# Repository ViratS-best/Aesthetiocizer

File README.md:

# Aesthetiocizer

Voice-controlled car firmware and hardware design for the Seeed XIAO RP2040. The firmware captures microphone audio, runs an Edge Impulse model, and uses recognized commands to control the car.

## Design

## Commands

The firmware responds to classifications with confidence of at least 0.85:
- `drive` starts the motors.
- `stop` stops the motors.
- `music` plays a melody through the speaker.
- `lights` flashes the LEDs.

## Project Contents

- `example-standalone-inferencing-pico-main/` contains the Pico application and its Edge Impulse inference sources.
- `viratsuper6-project-1-cpp-mcu-v1-impulse-#1/` contains the exported Edge Impulse model and inference SDK files.
- `design/` contains the KiCad schematic, PCB, project, BOM.csv, Gerber.zip, and 3D board export.
- `Screenshot *.png` files show project images.

## Bill of Materials (BOM)

| Part | Qty | Unit | Total | Vendor |
| :--- | :---: | :---: | :---: | :--- |
| [PCB Connection between all parts](https://www.jlcpcb.com) | 5 | $0.80 | $4.00 | [JLCPCB](https://www.jlcpcb.com) |
| [Seeed Studio XIAO RP2040 Microcontroller](https://www.amazon.com/dp/B0DRNTQ338) | 1 | $10.99 | $10.99 | [Amazon](https://www.amazon.com) |
| [Digital MEMS Microphone Module with PDM Output, MP34DT01](https://www.amazon.com/dp/B0HKML3MT8) | 1 | $9.29 | $9.29 | [Amazon](https://www.amazon.com) |
| Tax & shipping for the order | – | – | $5.00 | – |
| **Total** | | | **$29.28** | |

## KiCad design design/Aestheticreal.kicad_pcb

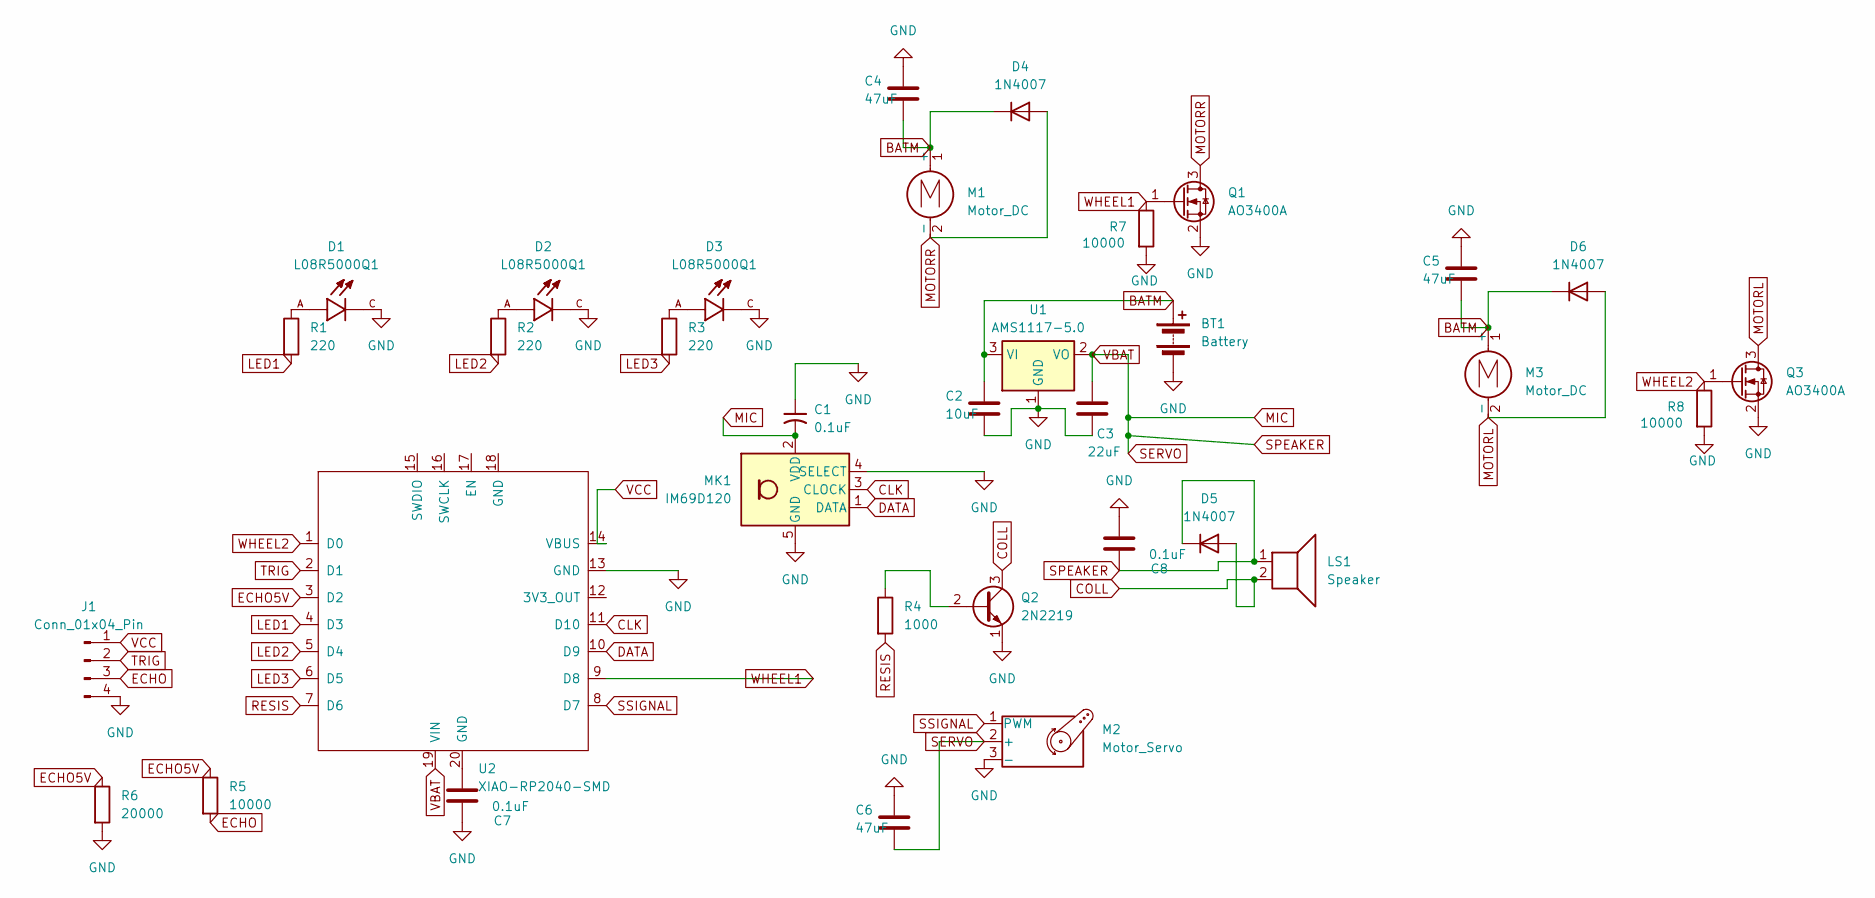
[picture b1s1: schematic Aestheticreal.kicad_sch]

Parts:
BT1: Battery; TerminalBlock_Phoenix_PT-1,5-2-3.5-H_1x02_P3.50mm_Horizontal
C1, C7, C8: 0.1uF; C_0805_2012Metric_Pad1.18x1.45mm_HandSolder
C2: 10uF; C_0805_2012Metric_Pad1.18x1.45mm_HandSolder
C3: 22uF; C_0805_2012Metric_Pad1.18x1.45mm_HandSolder
C4, C5, C6: 47uF; C_0805_2012Metric_Pad1.18x1.45mm_HandSolder
D1, D2, D3: L08R5000Q1; LEDRD254W57D500H1070; PARTREV NA
D4, D5, D6: 1N4007; D_DO-41_SOD81_P10.16mm_Horizontal
J1: Conn_01x04_Pin; PinHeader_1x04_P2.54mm_Vertical
LS1: Speaker; PinHeader_1x02_P2.54mm_Vertical
M1, M3: Motor_DC; TerminalBlock_Phoenix_PT-1,5-2-3.5-H_1x02_P3.50mm_Horizontal
M2: Motor_Servo; PinHeader_1x03_P2.54mm_Vertical
MK1: IM69D120; Infineon_PG-LLGA-5-1
Q1, Q3: AO3400A; SOT-23
Q2: 2N2219; TO-39-3
R1, R2, R3: 220; R_Axial_DIN0204_L3.6mm_D1.6mm_P5.08mm_Horizontal
R4: 1000; R_Axial_DIN0204_L3.6mm_D1.6mm_P5.08mm_Horizontal
R5, R7, R8: 10000; R_Axial_DIN0204_L3.6mm_D1.6mm_P5.08mm_Horizontal
R6: 20000; R_Axial_DIN0204_L3.6mm_D1.6mm_P5.08mm_Horizontal
U1: AMS1117-5.0; SOT-223-3_TabPin2
U2: XIAO-RP2040-SMD

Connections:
BATM: BT1.1 (+), C2.1, C4.2, C5.2, D4.1 (K), D6.1 (K), M1.1 (+), M3.1 (+), U1.3 (VI)
CLK: MK1.3 (CLOCK), U2.11 (D10)
COLL: D5.2 (A), LS1.2, Q2.3 (C)
DATA: MK1.1 (DATA), U2.10 (D9)
ECHO: J1.3, R5.2
ECHO5V: R5.1, R6.1, U2.3 (D2)
GND: BT1.2 (-), C1.1, C2.2, C3.2, C4.1, C5.1, C6.1, C7.2, C8.1, D1.C, D2.C, D3.C, J1.4, M2.3 (-), MK1.4 (SELECT), MK1.5 (GND), Q1.2 (S), Q2.1 (E), Q3.2 (S), R6.2, R7.2, R8.2, U1.1 (GND), U2.13 (GND)
LED1: R1.2, U2.4 (D3)
LED2: R2.2, U2.5 (D4)
LED3: R3.2, U2.6 (D5)
MIC: C1.2, C3.1, C6.2, C8.2, D5.1 (K), LS1.1, M2.2 (+), MK1.2 (VDD), U1.2 (VO), U2.19 (VIN)
MOTORL: D6.2 (A), M3.2 (-), Q3.3 (D)
MOTORR: D4.2 (A), M1.2 (-), Q1.3 (D)
unnamed: C7.1, U2.20 (GND)
unnamed: D1.A, R1.1
unnamed: D2.A, R2.1
unnamed: D3.A, R3.1
unnamed: Q2.2 (B), R4.1
RESIS: R4.2, U2.7 (D6)
SSIGNAL: M2.1 (PWM), U2.8 (D7)
TRIG: J1.2, U2.2 (D1)
VCC: J1.1, U2.14 (VBUS)
WHEEL1: Q1.1 (G), R7.1, U2.9 (D8)
WHEEL2: Q3.1 (G), R8.1, U2.1 (D0)

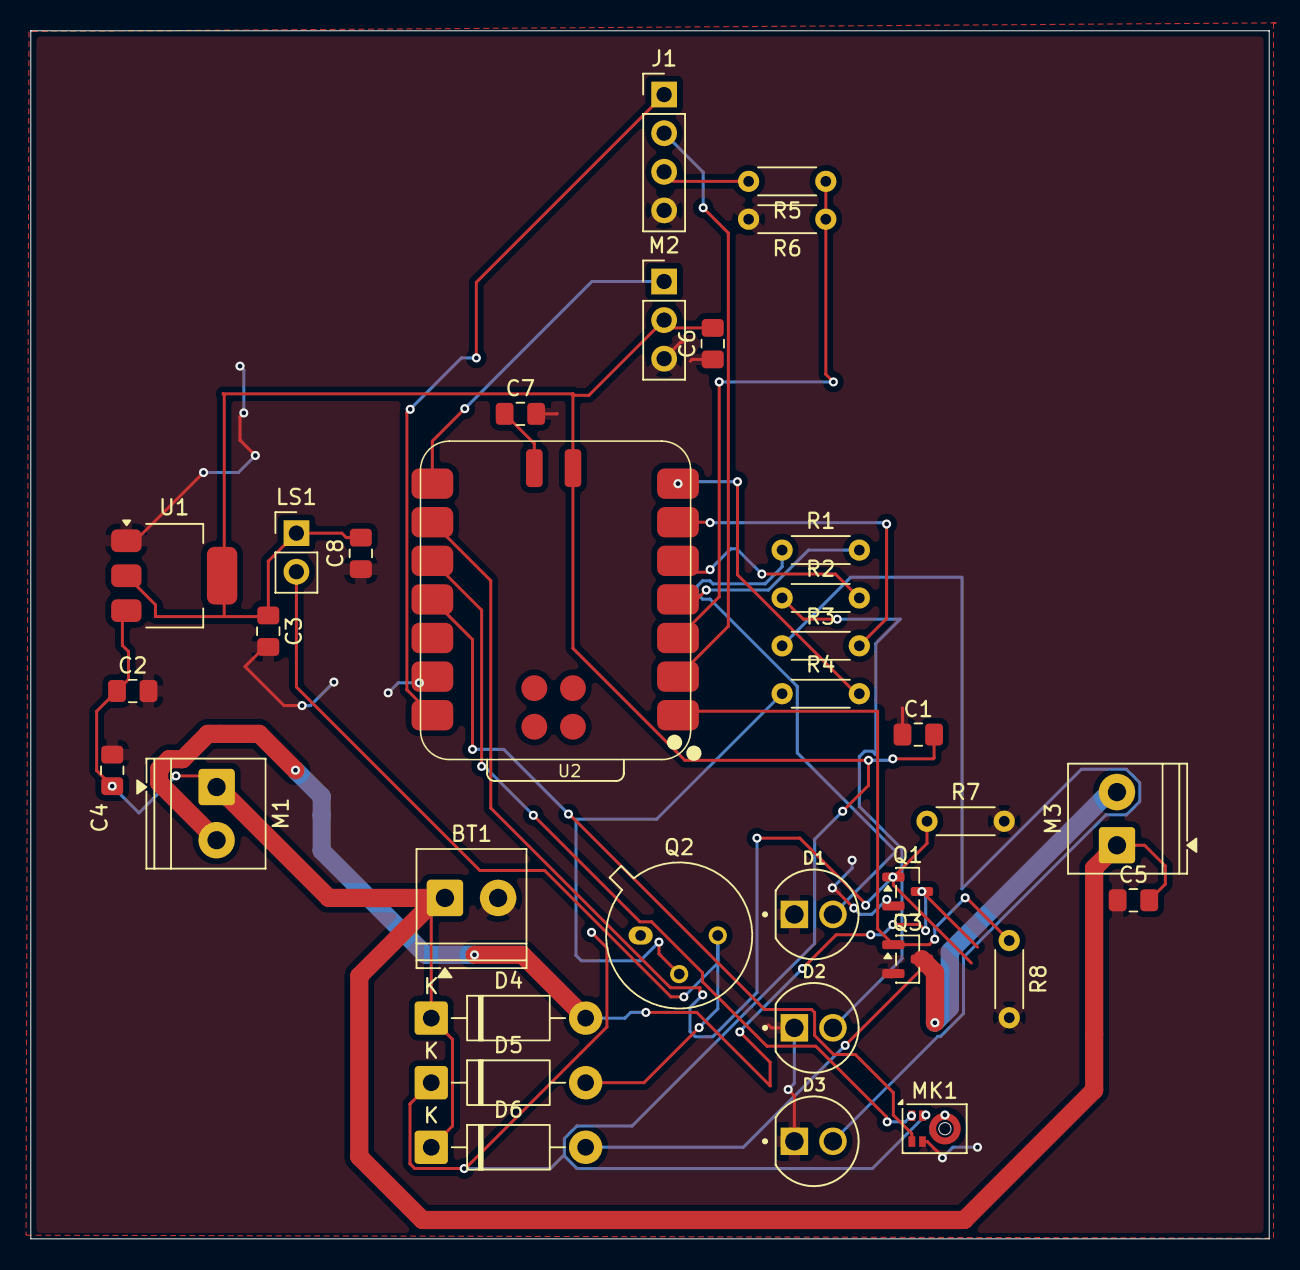
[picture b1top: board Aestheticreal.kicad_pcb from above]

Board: 2 copper layers, 81.5 x 79.5 mm, 34 parts (0 on the bottom side), 24 nets.

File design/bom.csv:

Designator,Footprint,Quantity,Value,LCSC Part #
BT1,"TerminalBlock_Phoenix_PT-1,5-2-3.5-H_1x02_P3.50mm_Horizontal",1,Battery,
"C1, C7, C8",0805,3,0.1uF,
C2,0805,1,10uF,
C3,0805,1,22uF,
"C4, C5, C6",0805,3,47uF,
"D1, D2, D3",LEDRD254W57D500H1070,3,L08R5000Q1,
"D4, D5, D6",D_DO-41_SOD81_P10.16mm_Horizontal,3,1N4007,
J1,PinHeader_1x04_P2.54mm_Vertical,1,Conn_01x04_Pin,
LS1,PinHeader_1x02_P2.54mm_Vertical,1,Speaker,
"M1, M3","TerminalBlock_Phoenix_PT-1,5-2-3.5-H_1x02_P3.50mm_Horizontal",2,Motor_DC,
M2,PinHeader_1x03_P2.54mm_Vertical,1,Motor_Servo,
MK1,Infineon_PG-LLGA-5-1,1,IM69D120,
"Q1, Q3",SOT-23,2,AO3400A,
Q2,TO-39-3,1,2N2219,
"R1, R2, R3",R_Axial_DIN0204_L3.6mm_D1.6mm_P5.08mm_Horizontal,3,220,
R4,R_Axial_DIN0204_L3.6mm_D1.6mm_P5.08mm_Horizontal,1,1000,
"R5, R7, R8",R_Axial_DIN0204_L3.6mm_D1.6mm_P5.08mm_Horizontal,3,10000,
R6,R_Axial_DIN0204_L3.6mm_D1.6mm_P5.08mm_Horizontal,1,20000,
U1,SOT-223-3_TabPin2,1,AMS1117-5.0,
U2,XIAO-RP2040-SMD,1,XIAO-RP2040-SMD,

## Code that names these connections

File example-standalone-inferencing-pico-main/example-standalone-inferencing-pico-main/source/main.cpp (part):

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const uint MOTOR_LEFT       = 26;
const uint ULTRASOUND_TRIG  = 27;
const uint ULTRASOUND_ECHO  = 28;
const uint LED1             = 29;
const uint LED2             = 6;
const uint LED3             = 7;
const uint SPEAKER          = 0;
const uint SERVO            = 1;
const uint MOTOR_RIGHT      = 2;
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        }
        if (strcmp(word, "drive") == 0) {
            is_driving = true;
            gpio_put(LED1, 1);
        } else if (strcmp(word, "stop") == 0) {
            is_driving = false;
            gpio_put(MOTOR_LEFT, 0);
            gpio_put(MOTOR_RIGHT, 0);
            gpio_put(LED1, 0);
        } else if (strcmp(word, "music") == 0) {
            play_rickroll();
        } else if (strcmp(word, "lights") == 0) {
            gpio_put(LED1, 1);
            gpio_put(LED2, 1);
            gpio_put(LED3, 1);
            sleep_ms(500);
            gpio_put(LED1, 0);
            gpio_put(LED2, 0);
            gpio_put(LED3, 0);
        }
    }
}
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    gpio_init(MOTOR_RIGHT);
    gpio_set_dir(MOTOR_RIGHT, GPIO_OUT);

    gpio_init(LED1); gpio_set_dir(LED1, GPIO_OUT);
    gpio_init(LED2); gpio_set_dir(LED2, GPIO_OUT);
    gpio_init(LED3); gpio_set_dir(LED3, GPIO_OUT);

    gpio_init(SPEAKER);
    gpio_set_dir(SPEAKER, GPIO_OUT);
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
